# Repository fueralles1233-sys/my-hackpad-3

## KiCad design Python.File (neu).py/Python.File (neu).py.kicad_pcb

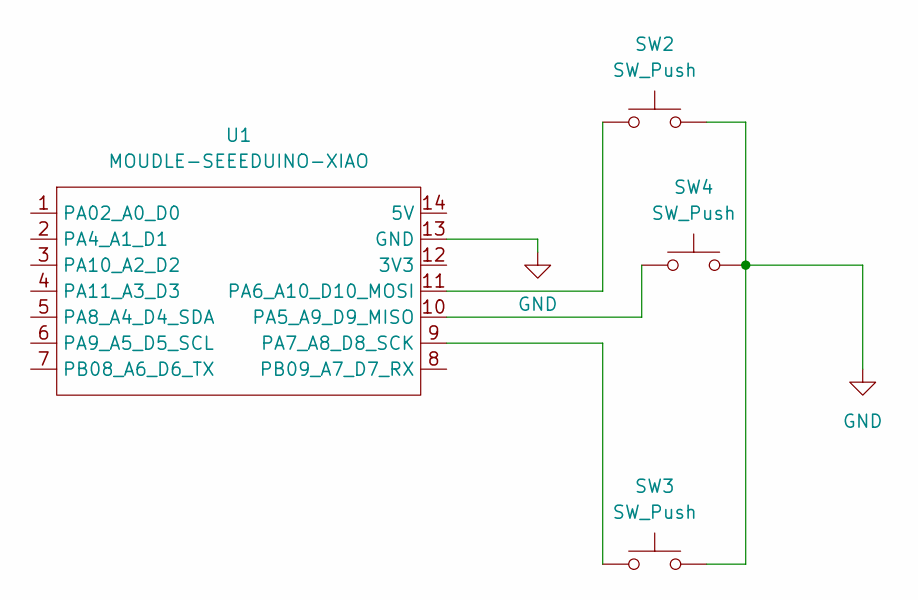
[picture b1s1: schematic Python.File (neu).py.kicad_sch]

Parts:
SW2, SW3, SW4: SW_Push; SW_Cherry_MX_1.00u_PCB
U1: MOUDLE-SEEEDUINO-XIAO; MCU_Seeed_ESP32C3

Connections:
GND: SW2.2, SW3.2, SW4.2, U1.13 (GND)
unnamed: SW4.1, U1.10 (PA5_A9_D9_MISO)
unnamed: SW2.1, U1.11 (PA6_A10_D10_MOSI)
unnamed: SW3.1, U1.9 (PA7_A8_D8_SCK)

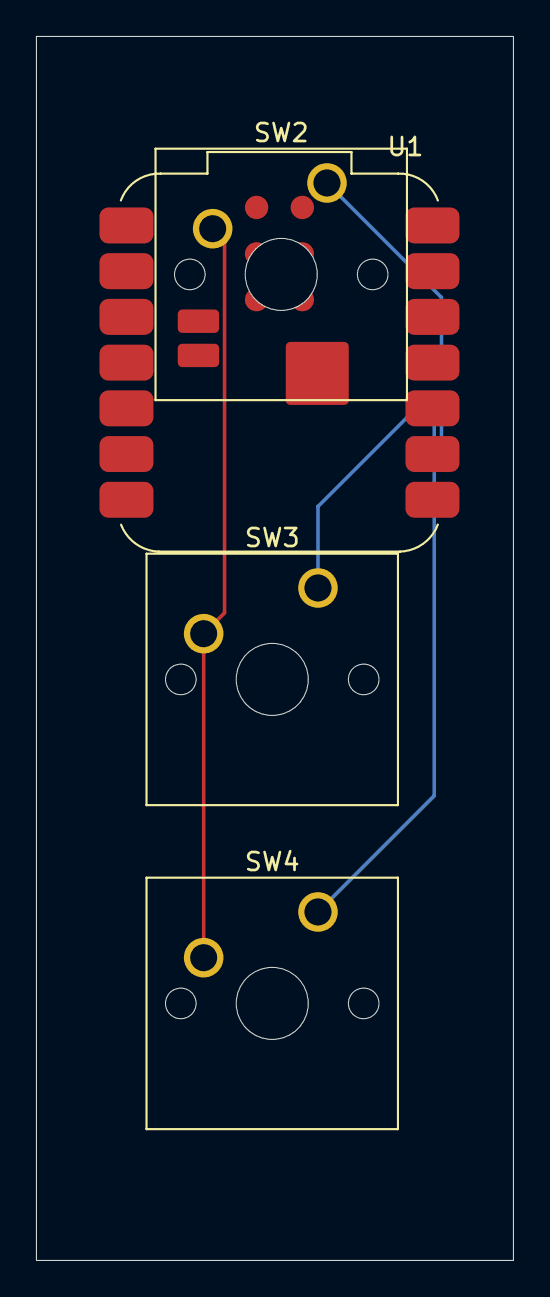
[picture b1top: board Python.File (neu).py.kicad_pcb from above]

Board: 2 copper layers, 26.5 x 68.0 mm, 4 parts (0 on the bottom side), 4 nets.
